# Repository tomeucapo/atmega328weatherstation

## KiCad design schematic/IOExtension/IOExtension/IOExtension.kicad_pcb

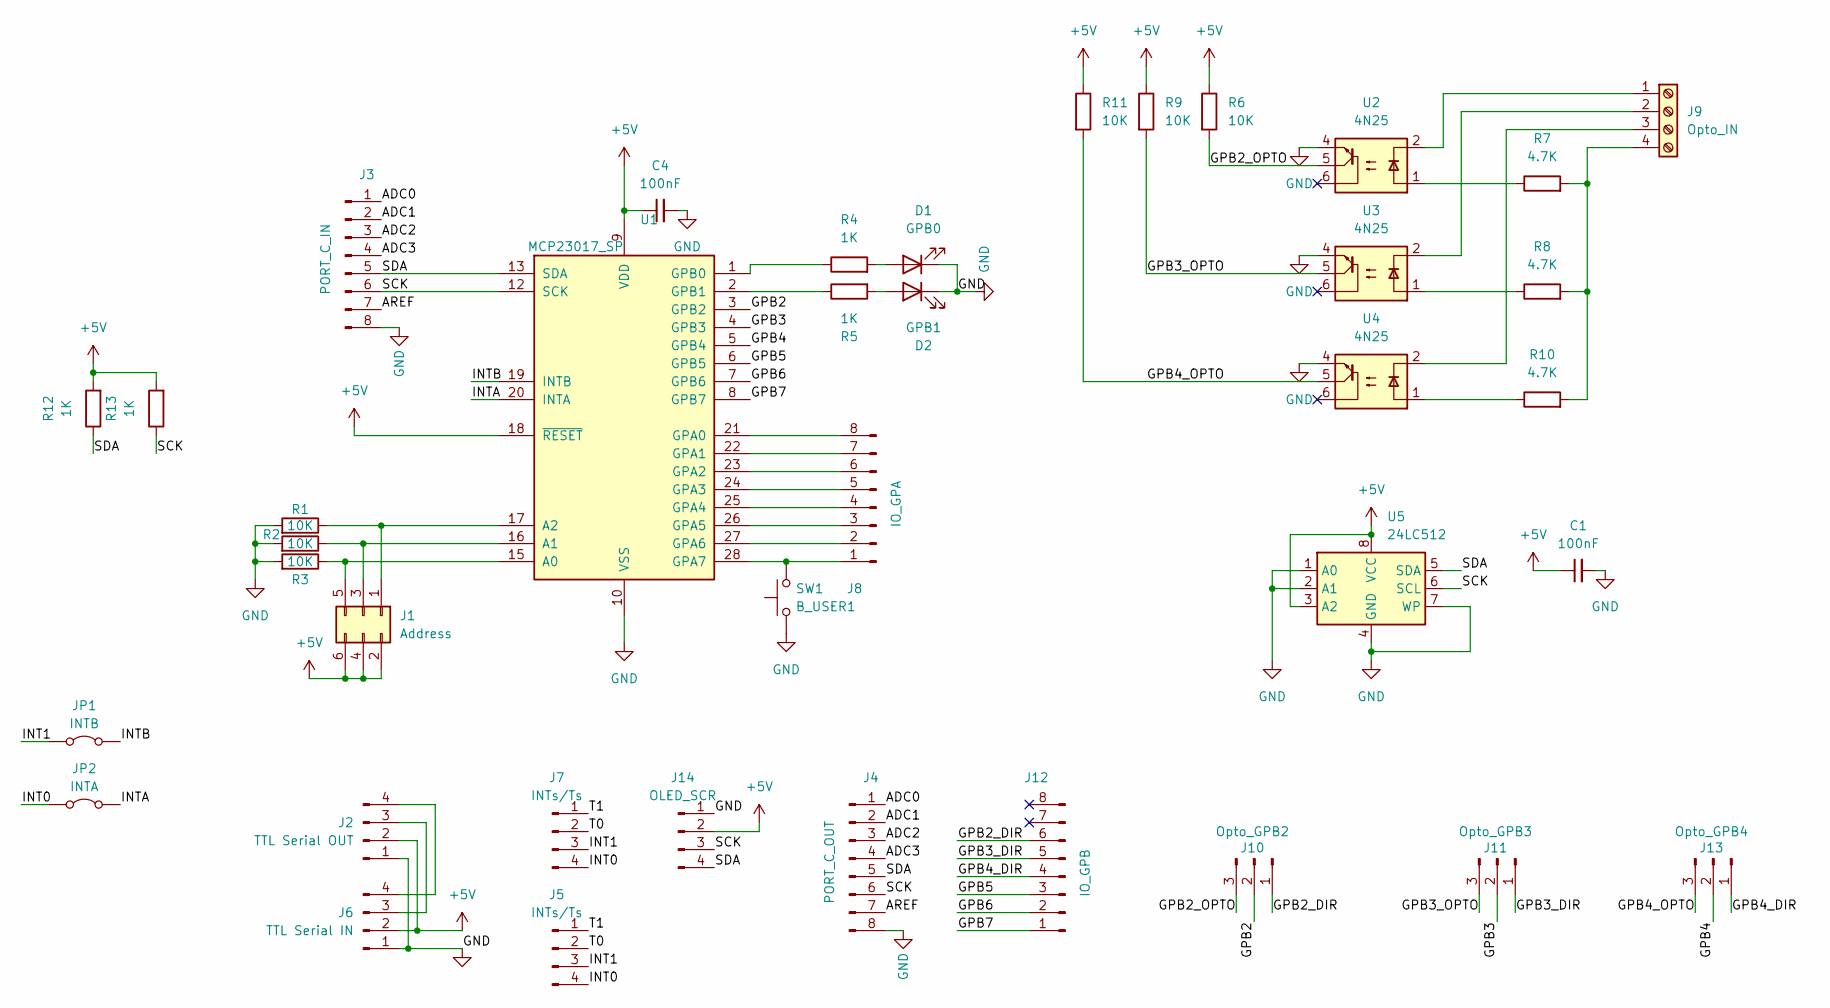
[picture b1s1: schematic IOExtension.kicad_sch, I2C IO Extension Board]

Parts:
C1, C4: 100nF; C_Disc_D7.0mm_W2.5mm_P5.00mm; MPN CK05BX104K; Farnell 1740547
D1: GPB0; LED_D3.0mm; Farnell 2984088
D2: GPB1; LED_D3.0mm; Farnell 3777906
J1: Address; PinHeader_2x03_P2.54mm_Vertical
J2: TTL Serial OUT; PinHeader_1x04_P2.54mm_Vertical
J3: PORT_C_IN; PinHeader_1x08_P2.54mm_Vertical
J4: PORT_C_OUT; PinHeader_1x08_P2.54mm_Vertical
J5, J7: INTs/Ts; PinHeader_1x04_P2.54mm_Vertical
J6: TTL Serial IN; PinHeader_1x04_P2.54mm_Vertical
J8: IO_GPA; PinHeader_1x08_P2.54mm_Vertical
J9: Opto_IN; TerminalBlock_Phoenix_MKDS-1,5-4-5.08_1x04_P5.08mm_Horizont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
J10: Opto_GPB2; PinHeader_1x03_P2.54mm_Vertical
J11: Opto_GPB3; PinHeader_1x03_P2.54mm_Vertical
J12: IO_GPB; PinHeader_1x06_P2.54mm_Vertical
J13: Opto_GPB4; PinHeader_1x03_P2.54mm_Vertical
J14: OLED_SCR; PinHeader_1x04_P2.54mm_Vertical
JP1: INTB; PinHeader_1x02_P2.54mm_Vertical
JP2: INTA; PinHeader_1x02_P2.54mm_Vertical
R1, R2, R3: 10K; R_Axial_DIN0204_L3.6mm_D1.6mm_P7.62mm_Horizontal; Farnell 9339051
R4, R5, R12, R13: 1K; R_Axial_DIN0204_L3.6mm_D1.6mm_P7.62mm_Horizontal; Farnell 9339051
R6, R9, R11: 10K; R_Axial_DIN0204_L3.6mm_D1.6mm_P7.62mm_Horizontal; Farnell 9339060
R7, R8, R10: 4.7K; R_Axial_DIN0204_L3.6mm_D1.6mm_P7.62mm_Horizontal; Farnell 9339540
SW1: B_USER1; SW_PUSH_6mm_H5mm
U1: MCP23017_SP; DIP-28_W7.62mm
U2, U3, U4: 4N25; DIP-6_W7.62mm; MPN CNY75A; Farnell 1045402
U5: 24LC512; DIP-8_W7.62mm

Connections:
+5V: C1.1, C4.1, J1.2, J1.4, J1.6, J2.2, J6.2, J14.2, R6.1, R9.1, R11.1, R12.2, R13.2, U1.9 (VDD), U1.18 (~RESET), U5.3 (A2), U5.8 (VCC)
/ADC0: J3.1, J4.1
/ADC1: J3.2, J4.2
/ADC2: J3.3, J4.3
/ADC3: J3.4, J4.4
/AREF: J3.7, J4.7
/GPB2: J10.2, U1.3 (GPB2)
/GPB2_DIR: J10.1, J12.6
/GPB2_OPTO: J10.3, R6.2, U2.5
/GPB3: J11.2, U1.4 (GPB3)
/GPB3_DIR: J11.1, J12.5
/GPB3_OPTO: J11.3, R9.2, U3.5
/GPB4: J13.2, U1.5 (GPB4)
/GPB4_DIR: J12.4, J13.1
/GPB4_OPTO: J13.3, R11.2, U4.5
/GPB5: J12.3, U1.6 (GPB5)
/GPB6: J12.2, U1.7 (GPB6)
/GPB7: J12.1, U1.8 (GPB7)
/INT0: J5.4, J7.4, JP2.1 (A)
/INT1: J5.3, J7.3, JP1.1 (A)
/INTA: JP2.2 (B), U1.20 (INTA)
/INTB: JP1.2 (B), U1.19 (INTB)
/SCK: J3.6, J4.6, J14.3, R13.1, U1.12 (SCK), U5.6 (SCL)
/SDA: J3.5, J4.5, J14.4, R12.1, U1.13 (SDA), U5.5 (SDA)
/T0: J5.2, J7.2
/T1: J5.1, J7.1
GND: C1.2, C4.2, D1.1 (K), D2.1 (K), J2.1, J3.8, J4.8, J6.1, J14.1, R1.2, R2.2, R3.2, SW1.1, U1.10 (VSS), U2.4, U3.4, U4.4, U5.1 (A0), U5.2 (A1), U5.4 (GND), U5.7 (WP)
unnamed: D1.2 (A), R4.2
unnamed: D2.2 (A), R5.2
unnamed: J1.1, R1.1, U1.17 (A2)
unnamed: J1.3, R2.1, U1.16 (A1)
unnamed: J1.5, R3.1, U1.15 (A0)
unnamed: J2.3, J6.3
unnamed: J2.4, J6.4
unnamed: J8.1, SW1.2, U1.28 (GPA7)
unnamed: J8.2, U1.27 (GPA6)
unnamed: J8.3, U1.26 (GPA5)
unnamed: J8.4, U1.25 (GPA4)
unnamed: J8.5, U1.24 (GPA3)
unnamed: J8.6, U1.23 (GPA2)
unnamed: J8.7, U1.22 (GPA1)
unnamed: J8.8, U1.21 (GPA0)
unnamed: J9.1, U2.2
unnamed: J9.2, U3.2
unnamed: J9.3, U4.2
unnamed: J9.4, R7.2, R8.2, R10.2
unnamed: R7.1, U2.1
unnamed: R8.1, U3.1
unnamed: R10.1, U4.1
unnamed: R4.1, U1.1 (GPB0)
unnamed: R5.1, U1.2 (GPB1)

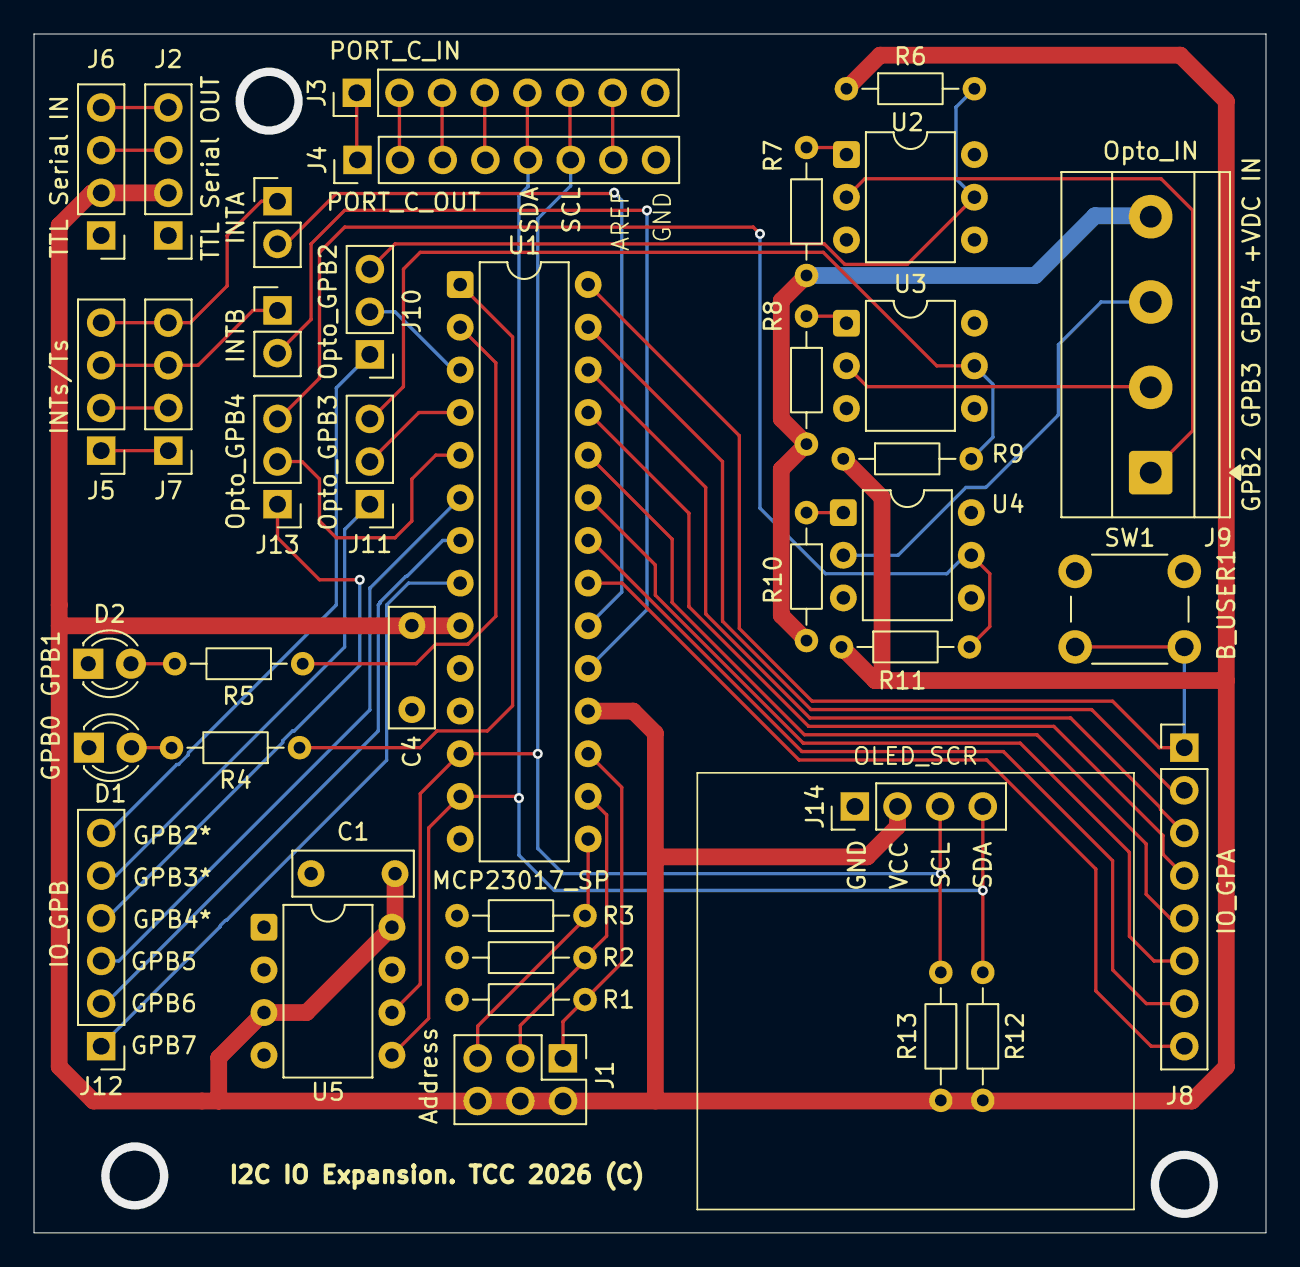
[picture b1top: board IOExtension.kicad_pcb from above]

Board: 2 copper layers, 73.4 x 71.4 mm, 39 parts (0 on the bottom side), 51 nets.

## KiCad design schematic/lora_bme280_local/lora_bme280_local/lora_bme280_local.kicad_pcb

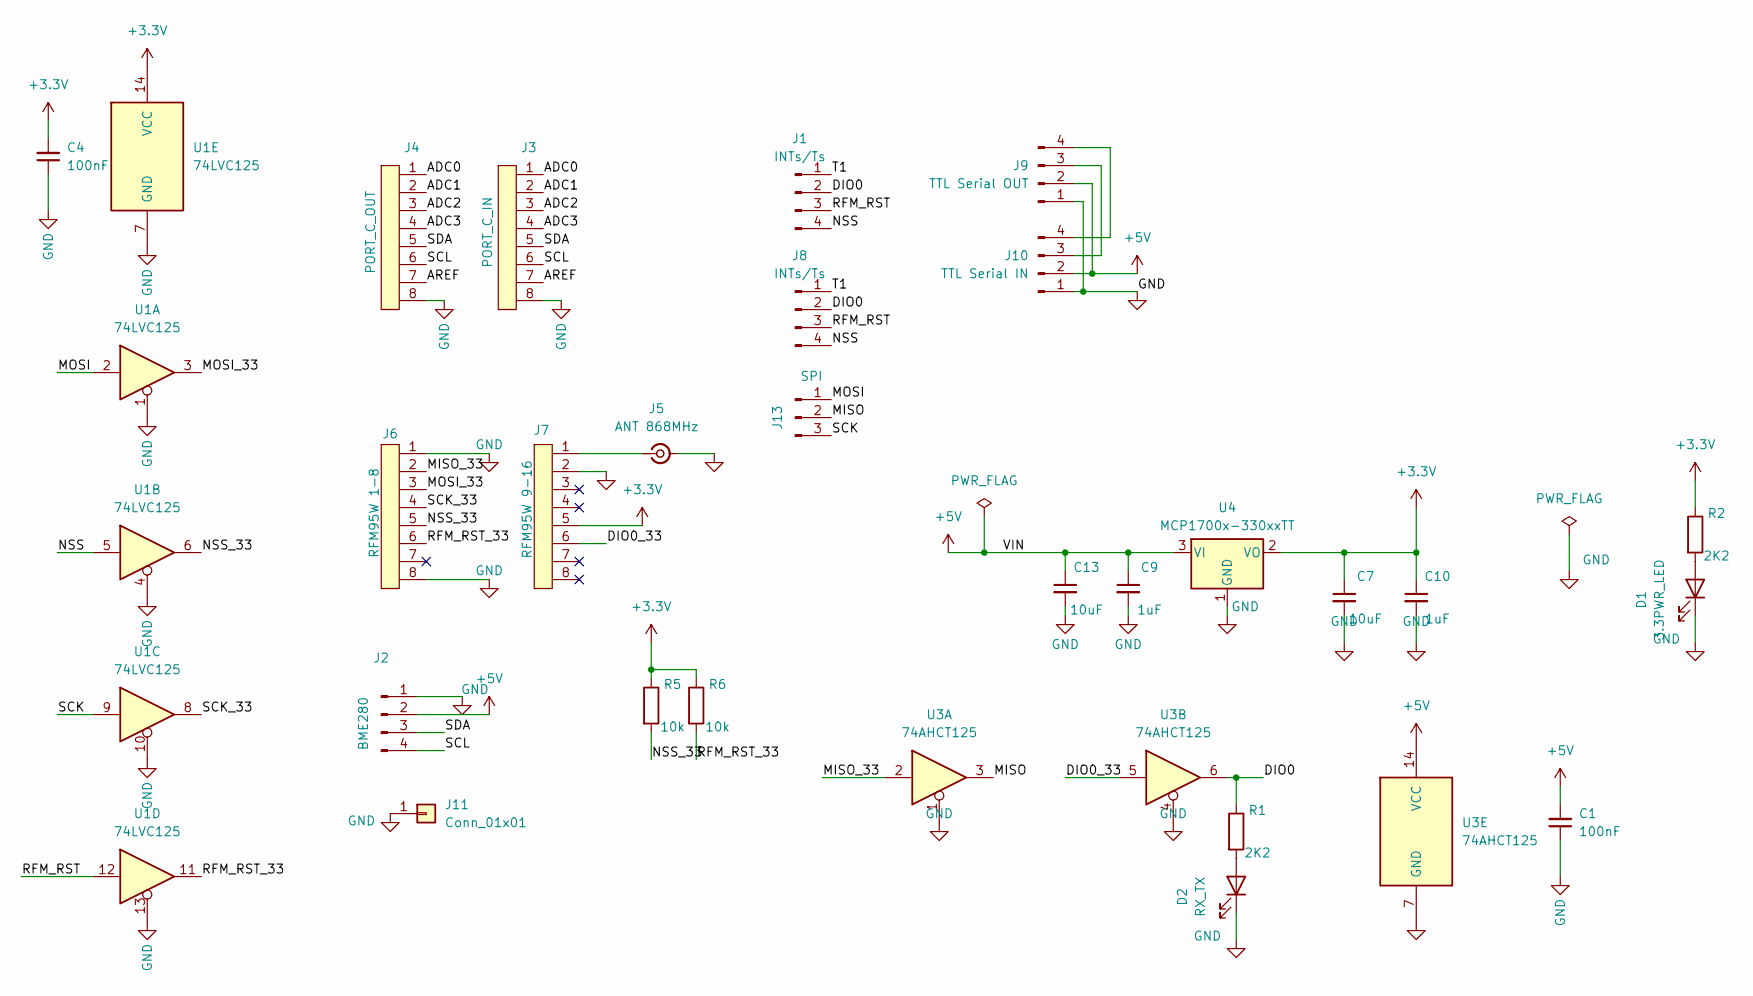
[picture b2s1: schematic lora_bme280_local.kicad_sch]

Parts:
C1: 100nF; C_Disc_D7.0mm_W2.5mm_P5.00mm; MPN CK05BX104K; Farnell 1740547
C4: 100nF; C_0805_2012Metric_Pad1.18x1.45mm_HandSolder; MPN CK05BX104K; Farnell 1740547
C7, C13: 10uF; C_0805_2012Metric
C9, C10: 1uF; C_0805_2012Metric
D1: 3.3PWR_LED; LED_D3.0mm; Farnell 3777906
D2: RX_TX; LED_D3.0mm; Farnell 3777906
J1, J8: INTs/Ts; PinHeader_1x04_P2.54mm_Vertical
J2: BME280; NS-Tech_Grove_1x04_P2mm_Vertical
J3: PORT_C_IN; PinHeader_1x08_P2.54mm_Vertical
J4: PORT_C_OUT; PinHeader_1x08_P2.54mm_Vertical
J5: ANT 868MHz; SMA_Amphenol_132134-11_Vertical
J6: RFM95W 1-8; PinHeader_1x08_P2.00mm_Vertical
J7: RFM95W 9-16; PinHeader_1x08_P2.00mm_Vertical
J9: TTL Serial OUT; PinHeader_1x04_P2.54mm_Vertical
J10: TTL Serial IN; PinHeader_1x04_P2.54mm_Vertical
J11: Conn_01x01; MountingHole_3mm_Pad
J13: SPI; PinHeader_1x03_P2.54mm_Vertical
R1, R2: 2K2; R_Axial_DIN0204_L3.6mm_D1.6mm_P7.62mm_Horizontal
R5, R6: 10k; R_Axial_DIN0204_L3.6mm_D1.6mm_P7.62mm_Horizontal
U1: 74LVC125; TSSOP-14_4.4x5mm_P0.65mm
U3: 74AHCT125; DIP-14_W7.62mm
U4: MCP1700x-330xxTT; SOT-23

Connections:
+3.3V: C4.2, C7.1, C10.1, J7.5, R2.1, R5.1, R6.1, U1.14 (VCC), U4.2 (VO)
+5V: C1.2, C9.1, C13.1, J2.2, J9.2, J10.2, U3.14 (VCC), U4.3 (VI)
/ADC0: J3.1, J4.1
/ADC1: J3.2, J4.2
/ADC2: J3.3, J4.3
/ADC3: J3.4, J4.4
/AREF: J3.7, J4.7
/DIO0: J1.2, J8.2, R1.1, U3.6
/DIO0_33: J7.6, U3.5
/MISO: J13.2, U3.3
/MISO_33: J6.2, U3.2
/MOSI: J13.1, U1.2
/MOSI_33: J6.3, U1.3
/NSS: J1.4, J8.4, U1.5
/NSS_33: J6.5, R5.2, U1.6
/RFM_RST: J1.3, J8.3, U1.12
/RFM_RST_33: J6.6, R6.2, U1.11
/SCK: J13.3, U1.9
/SCK_33: J6.4, U1.8
/SCL: J2.4, J3.6, J4.6
/SDA: J2.3, J3.5, J4.5
/T1: J1.1, J8.1
GND: C1.1, C4.1, C7.2, C9.2, C10.2, C13.2, D1.1 (K), D2.1 (K), J2.1, J3.8, J4.8, J5.2 (Ext), J6.1, J6.8, J7.2, J9.1, J10.1, J11.1, U1.1, U1.4, U1.7 (GND), U1.10, U1.13, U3.1, U3.4, U3.7 (GND), U4.1 (GND)
unnamed: D1.2 (A), R2.2
unnamed: D2.2 (A), R1.2
unnamed: J5.1 (In), J7.1
unnamed: J9.3, J10.3
unnamed: J9.4, J10.4

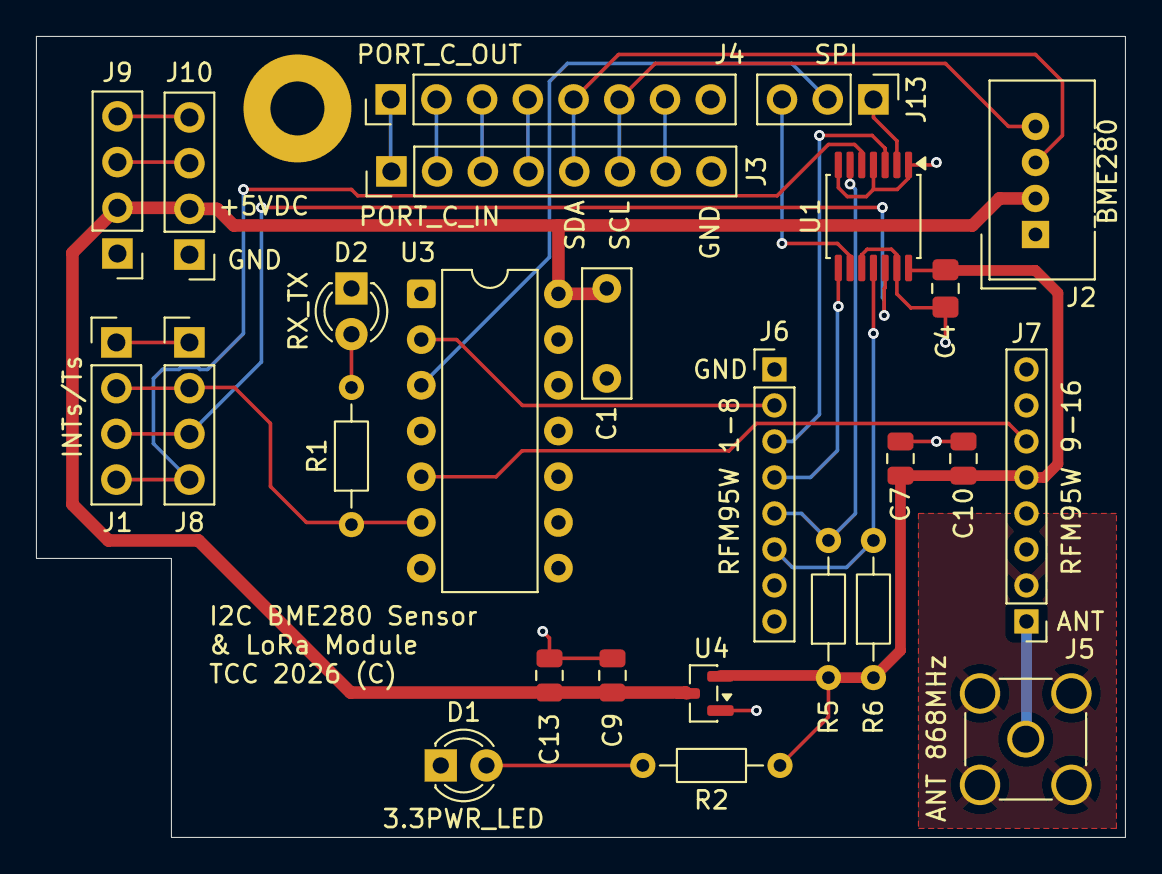
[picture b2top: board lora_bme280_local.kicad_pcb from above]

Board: 2 copper layers, 60.5 x 44.5 mm, 27 parts (0 on the bottom side), 28 nets.

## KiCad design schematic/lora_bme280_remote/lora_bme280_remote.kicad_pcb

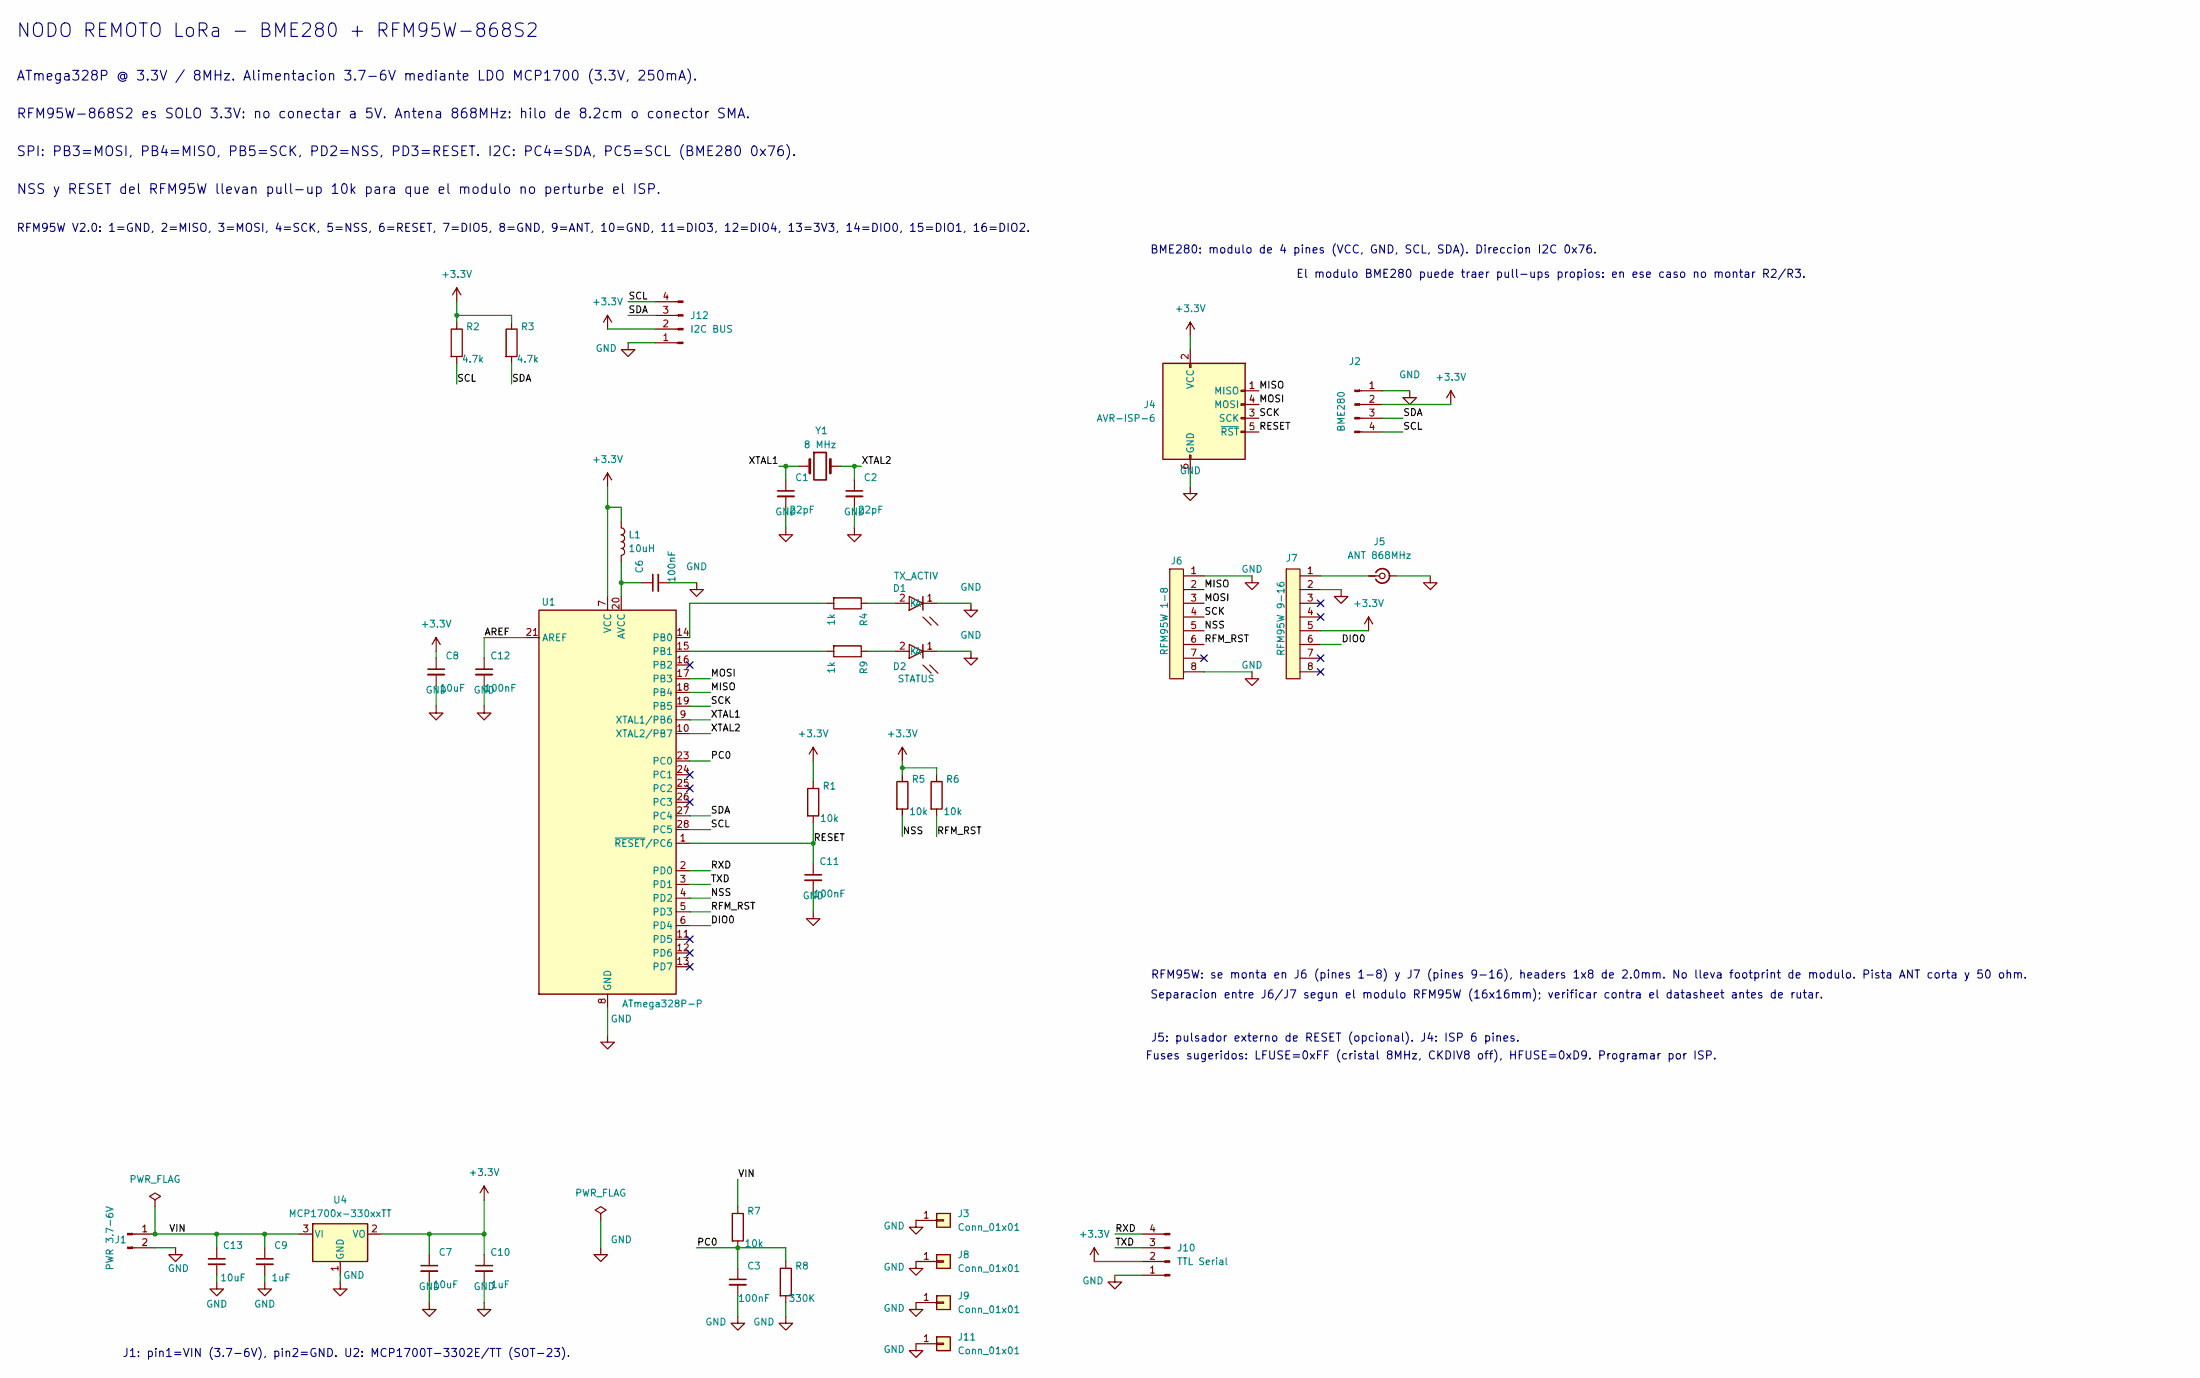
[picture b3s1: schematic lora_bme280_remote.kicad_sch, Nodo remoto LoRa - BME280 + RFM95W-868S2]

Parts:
C1, C2: 22pF; C_Disc_D4.3mm_W1.9mm_P5.00mm
C3, C6, C11, C12: 100nF; C_Disc_D7.0mm_W2.5mm_P5.00mm
C7, C13: 10uF; C_0805_2012Metric
C8: 10uF; C_Disc_D7.0mm_W2.5mm_P5.00mm
C9, C10: 1uF; C_0805_2012Metric
D1: TX_ACTIV; LED_D3.0mm
D2: STATUS; LED_D3.0mm
J1: PWR 3.7-6V; JST_EH_B2B-EH-A_1x02_P2.50mm_Vertical
J2: BME280; NS-Tech_Grove_1x04_P2mm_Vertical
J3, J8, J9, J11: Conn_01x01; MountingHole_3mm_Pad
J4: AVR-ISP-6; IDC-Header_2x03_P2.54mm_Vertical; MPN 75869-131LF; Farnell 2293757
J5: ANT 868MHz; SMA_Amphenol_132134_Vertical
J6: RFM95W 1-8; PinHeader_1x08_P2.00mm_Vertical
J7: RFM95W 9-16; PinHeader_1x08_P2.00mm_Vertical
J10: TTL Serial; PinHeader_1x04_P2.54mm_Vertical
J12: I2C BUS; PinHeader_1x04_P2.54mm_Vertical
L1: 10uH; L_Axial_L5.3mm_D2.2mm_P10.16mm_Horizontal_Vishay_IM-1; MPN 77F100K-TR-RC; Farnell 2924990
R1, R5, R6, R7: 10k; R_Axial_DIN0204_L3.6mm_D1.6mm_P7.62mm_Horizontal
R2, R3: 4.7k; R_Axial_DIN0204_L3.6mm_D1.6mm_P7.62mm_Horizontal
R4, R9: 1k; R_Axial_DIN0204_L3.6mm_D1.6mm_P7.62mm_Horizontal
R8: 330K; R_Axial_DIN0204_L3.6mm_D1.6mm_P7.62mm_Horizontal
U1: ATmega328P-P; DIP-28_W7.62mm; MPN ATMEGA328P-PU; Farnell 1715487
U4: MCP1700x-330xxTT; SOT-23
Y1: 8 MHz; Crystal_HC49-U_Vertical

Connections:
+3.3V: C7.1, C8.1, C10.1, J2.2, J4.2 (VCC), J7.5, J10.2, J12.2, L1.1, R1.1, R2.1, R3.1, R5.1, R6.1, U1.7 (VCC), U4.2 (VO)
/AREF: C12.1, U1.21 (AREF)
/DIO0: J7.6, U1.6 (PD4)
/MISO: J4.1 (MISO), J6.2, U1.18 (PB4)
/MOSI: J4.4 (MOSI), J6.3, U1.17 (PB3)
/NSS: J6.5, R5.2, U1.4 (PD2)
/PC0: C3.1, R7.2, R8.1, U1.23 (PC0)
/RESET: C11.1, J4.5 (~RST), R1.2, U1.1 (~RESET/PC6)
/RFM_RST: J6.6, R6.2, U1.5 (PD3)
/RXD: J10.4, U1.2 (PD0)
/SCK: J4.3 (SCK), J6.4, U1.19 (PB5)
/SCL: J2.4, J12.4, R2.2, U1.28 (PC5)
/SDA: J2.3, J12.3, R3.2, U1.27 (PC4)
/TXD: J10.3, U1.3 (PD1)
/VIN: C9.1, C13.1, J1.1, R7.1, U4.3 (VI)
/XTAL1: C1.1, U1.9 (XTAL1/PB6), Y1.1
/XTAL2: C2.1, U1.10 (XTAL2/PB7), Y1.2
GND: C1.2, C2.2, C3.2, C6.2, C7.2, C8.2, C9.2, C10.2, C11.2, C12.2, C13.2, D1.1 (K), D2.1 (K), J1.2, J2.1, J3.1, J4.6 (GND), J5.2 (Ext), J6.1, J6.8, J7.2, J8.1, J9.1, J10.1, J11.1, J12.1, R8.2, U1.8 (GND), U1.22 (GND), U4.1 (GND)
unnamed: D1.2 (A), R4.1
unnamed: D2.2 (A), R9.1
unnamed: J5.1 (In), J7.1
unnamed: C6.1, L1.2, U1.20 (AVCC)
unnamed: R4.2, U1.14 (PB0)
unnamed: R9.2, U1.15 (PB1)

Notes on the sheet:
ATmega328P @ 3.3V / 8MHz. Alimentacion 3.7-6V mediante LDO MCP1700 (3.3V, 250mA).
RFM95W-868S2 es SOLO 3.3V: no conectar a 5V. Antena 868MHz: hilo de 8.2cm o conector SMA.
BME280: modulo de 4 pines (VCC, GND, SCL, SDA). Direccion I2C 0x76.
NODO REMOTO LoRa - BME280 + RFM95W-868S2
RFM95W: se monta en J6 (pines 1-8) y J7 (pines 9-16), headers 1x8 de 2.0mm. No lleva footprint de modulo. Pista ANT corta y 50 ohm.
SPI: PB3=MOSI, PB4=MISO, PB5=SCK, PD2=NSS, PD3=RESET. I2C: PC4=SDA, PC5=SCL (BME280 0x76).
J5: pulsador externo de RESET (opcional). J4: ISP 6 pines.
Separacion entre J6/J7 segun el modulo RFM95W (16x16mm); verificar contra el datasheet antes de rutar.
Fuses sugeridos: LFUSE=0xFF (cristal 8MHz, CKDIV8 off), HFUSE=0xD9. Programar por ISP.
El modulo BME280 puede traer pull-ups propios: en ese caso no montar R2/R3.
J1: pin1=VIN (3.7-6V), pin2=GND. U2: MCP1700T-3302E/TT (SOT-23).
RFM95W V2.0: 1=GND, 2=MISO, 3=MOSI, 4=SCK, 5=NSS, 6=RESET, 7=DIO5, 8=GND, 9=ANT, 10=GND, 11=DIO3, 12=DIO4, 13=3V3, 14=DIO0, 15=DIO1, 16=DIO2.
NSS y RESET del RFM95W llevan pull-up 10k para que el modulo no perturbe el ISP.

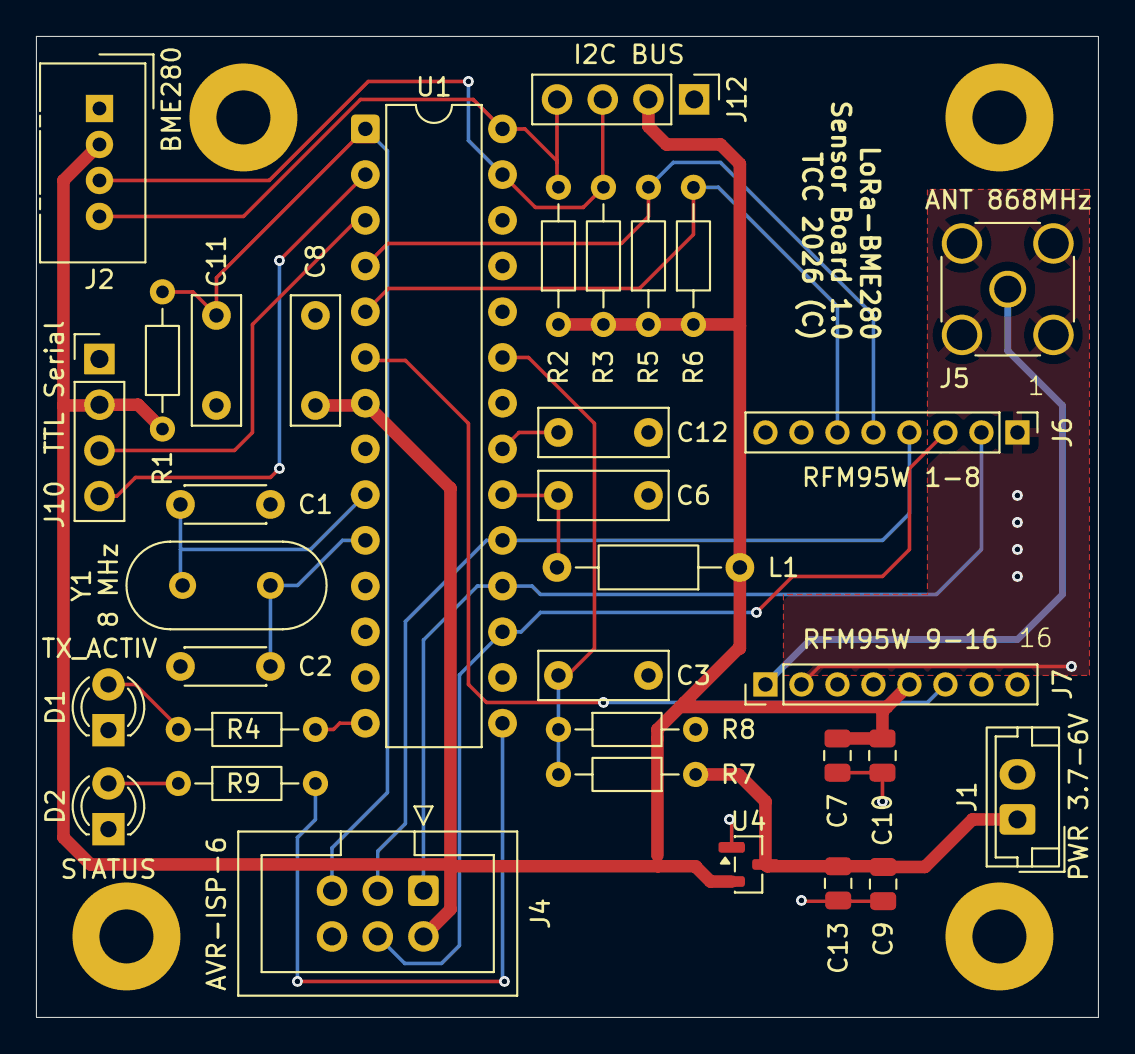
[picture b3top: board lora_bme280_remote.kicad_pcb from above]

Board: 2 copper layers, 59.0 x 54.5 mm, 38 parts (0 on the bottom side), 24 nets.

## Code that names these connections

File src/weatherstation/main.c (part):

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
// ======================================================
// PLUVIOMETRO
// PB1 = PCINT1
// CONTACTO NC
// ======================================================

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        ultoa(SX127X_FREQ_HZ, frequency, 10);
        uart_tx_string(frequency);
        uart_tx_string_P(PSTR("\r\nSPI=MODE0,MSB,F_CPU/16\r\n"));
        uart_tx_string_P(PSTR("PINS: CS=PD5 RESET=PD4 DIO0=PD3 MOSI=PB3 MISO=PB4 SCK=PB5\r\n"));
        uart_tx_string_P(PSTR("REG_OP_MODE=0x"));
        uart_tx_char(hex[(op_mode >> 4) & 0x0F]);
        uart_tx_char(hex[op_mode & 0x0F]);
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    twi_bus_recover();
    _delay_ms(150);

    // MCP23017 (PC4=SDA, PC5=SCL). mcp23017_init() ya deja GPA7 como
    // entrada (pulsador a masa) y el resto como salidas.
    mcp23017_init();
    mcp23017_pullup(MCP23017_PORTA, (1 << BTN_MCP_PIN)); // pull-up en GPA7
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    bme_present = bme280_init();
    pred_init();

    // Radio local LoRa: DIO0=PD3, RESET=PD4, CS/NSS=PD5; SPI por hardware.
    lora_present = sx127x_init();

    welcome();
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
